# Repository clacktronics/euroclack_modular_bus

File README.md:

# Euroclack Modular Power

The set of boards in this repository are designed for building the power bus for a Eurorack synthesizer. They have been produced within the constraints of 100x100mm which is the size cheap PCB pool manufacturers usually use for their cheapest service.

| Folder   | Type   | Description   | Status  |
| -------- | ------ | ------------- | --------|
| 5V_supply   | DC/DC supply | Will produce a 5v rail on the power bus from 12V | Untested prototype |
| 6_way_bus | Utility | 6 way extension of eurorack IDC | Untested prototype |
| barrel_jack_panel | Panel | Barrel input for DC voltage or AC wall wart | Not Started |
| delay_start | Utility | Takes in power and outputs power at a delay | Not Started |
| linear_pu | AC/DC supply | Traditional Linear PSU | Untested prototype |
| meanwell_rddw20f-12_psu | DC/DC supply | Takes a single supply and output +-12V | Layout |
| switch_status_panel | Utility | simple panel that shows LED for power rails and switch for turning on and off | Not started|
| wall_wart_linear_psu | AC/DC supply | when no centre tap available, for example an AC wall wart or non-CT transformer. | Not started |

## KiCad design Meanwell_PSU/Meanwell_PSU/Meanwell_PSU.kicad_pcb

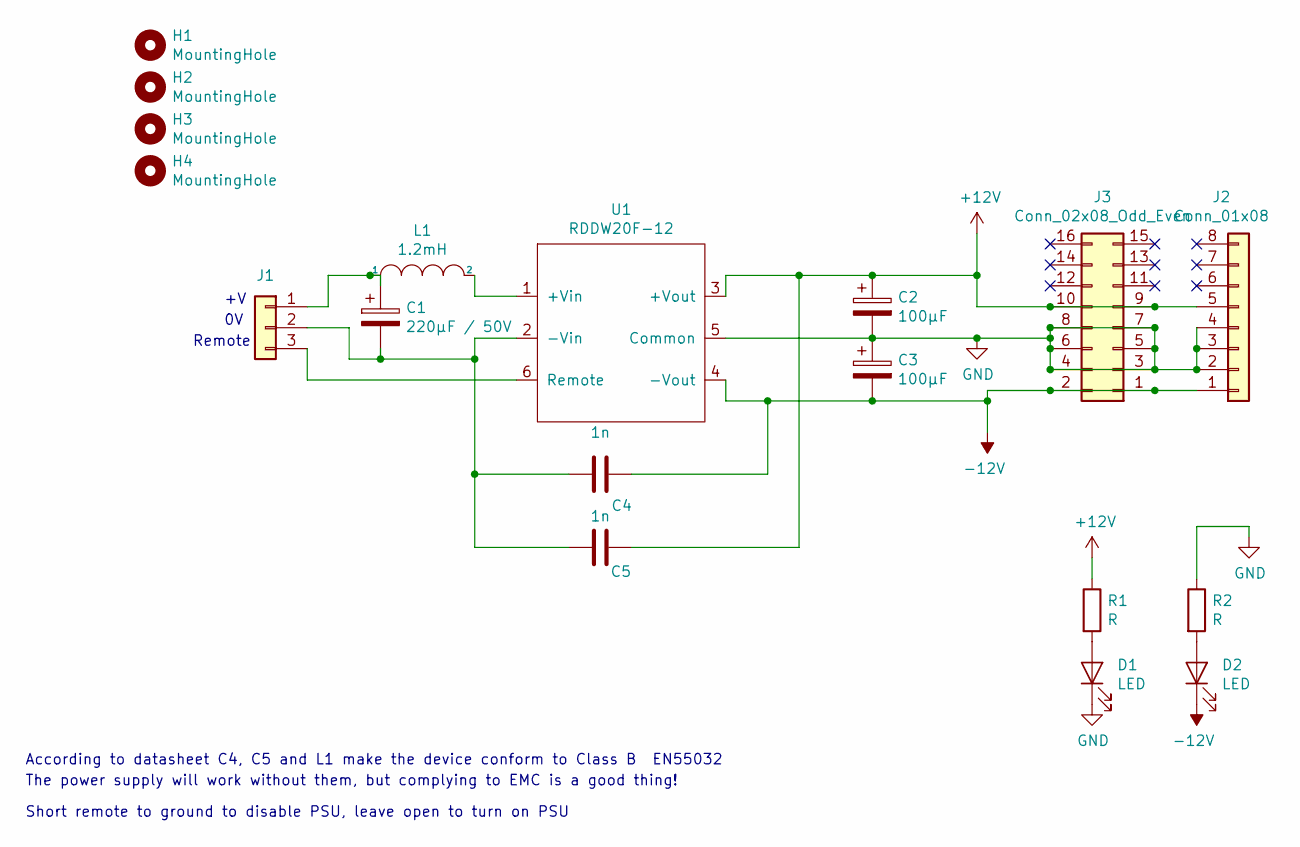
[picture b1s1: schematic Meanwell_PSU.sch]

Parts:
C1: 220μF / 50V; C_TH_Elec_5mm_P2mm
C2, C3: 100μF; C_TH_Elec_5mm_P2mm
C4, C5: 1n; C_TH_Disc_P5.00mm
D1, D2: LED; LED_D3.0mm
H1, H2, H3, H4: MountingHole; MountingHole_3.2mm_M3
J1: Conn_01x03; PhoenixContact_MSTBA_2,5_3-G-5,08_1x03_P5.08mm_Horizontal
J2: Conn_01x08; PinSocket_1x08_P2.54mm_Vertical
J3: Conn_02x08_Odd_Even; Eurorack-IDC-Header
L1: 1.2mH; L_Radial_D7.0mm_P3.00mm
R1, R2: R; R_TH_Axial_250mw_P10.16mm_Horizontal
U1: RDDW20F-12; RDDW20F

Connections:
+12V: C2.1, C5.1, J2.5, J3.9, J3.10, R1.1, U1.3 (+Vout)
-12V: C3.2, C4.1, D2.1 (K), J2.1, J3.1, J3.2, U1.4 (-Vout)
GND: C2.2, C3.1, D1.1 (K), J2.2, J2.3, J2.4, J3.3, J3.4, J3.5, J3.6, J3.7, J3.8, R2.1, U1.5 (Common)
unnamed: C1.1, J1.1, L1.1
unnamed: C1.2, C4.2, C5.2, J1.2, U1.2 (-Vin)
unnamed: D1.2 (A), R1.2
unnamed: D2.2 (A), R2.2
unnamed: J1.3, U1.6 (Remote)
unnamed: L1.2, U1.1 (+Vin)

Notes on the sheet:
Remote
According to datasheet C4, C5 and L1 make the device conform to Class B EN55032
The power supply will work without them, but complying to EMC is a good thing!
Short remote to ground to disable PSU, leave open to turn on PSU

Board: 2 copper layers, 18 parts (0 on the bottom side), 9 nets, no tracks yet.

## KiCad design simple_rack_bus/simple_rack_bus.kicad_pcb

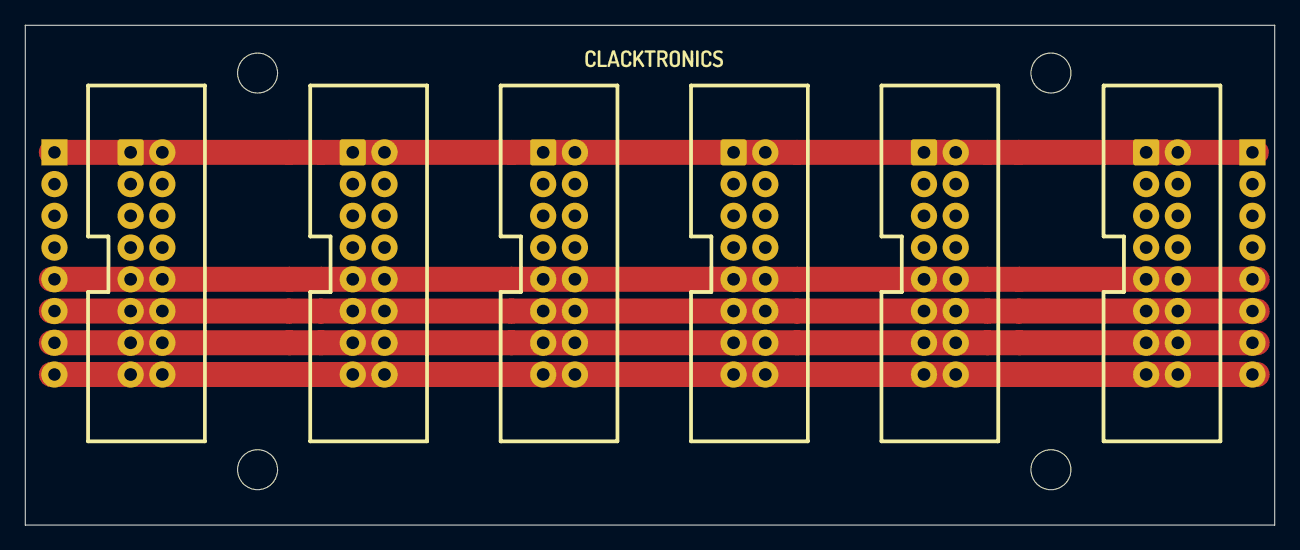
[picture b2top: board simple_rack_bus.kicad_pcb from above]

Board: 2 copper layers, 100.0 x 40.0 mm, 12 parts (0 on the bottom side), 6 nets.

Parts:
H1, H2, H3, H4: MountingHole; MountingHole_3.2mm_M3
J1, J2, J3, J4, J5, J6: Conn_02x08_Odd_Even; Eurorack-IDC-Header
J7, J8: Conn_01x08; PinHeader_1x08_P2.54mm_Vertical

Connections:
-12V: J1.1, J1.2, J2.1, J2.2, J3.1, J3.2, J4.1, J4.2, J5.1, J5.2, J6.1, J6.2, J7.1, J8.1
GND: J1.3, J1.4, J1.5, J1.6, J1.7, J1.8, J2.3, J2.4, J2.5, J2.6, J2.7, J2.8, J3.3, J3.4, J3.5, J3.6, J3.7, J3.8, J4.3, J4.4, J4.5, J4.6, J4.7, J4.8, J5.3, J5.4, J5.5, J5.6, J5.7, J5.8, J6.3, J6.4, J6.5, J6.6, J6.7, J6.8, J7.2, J7.3, J7.4, J8.2, J8.3, J8.4
unnamed: J1.9, J1.10, J2.9, J2.10, J3.9, J3.10, J4.9, J4.10, J5.9, J5.10, J6.9, J6.10, J7.5, J8.5
unnamed: J1.11, J1.12, J2.11, J2.12, J3.11, J3.12, J4.11, J4.12, J5.11, J5.12, J6.11, J6.12, J7.6, J8.6
unnamed: J1.13, J1.14, J2.13, J2.14, J3.13, J3.14, J4.13, J4.14, J5.13, J5.14, J6.13, J6.14, J7.7, J8.7
unnamed: J1.15, J1.16, J2.15, J2.16, J3.15, J3.16, J4.15, J4.16, J5.15, J5.16, J6.15, J6.16, J7.8, J8.8

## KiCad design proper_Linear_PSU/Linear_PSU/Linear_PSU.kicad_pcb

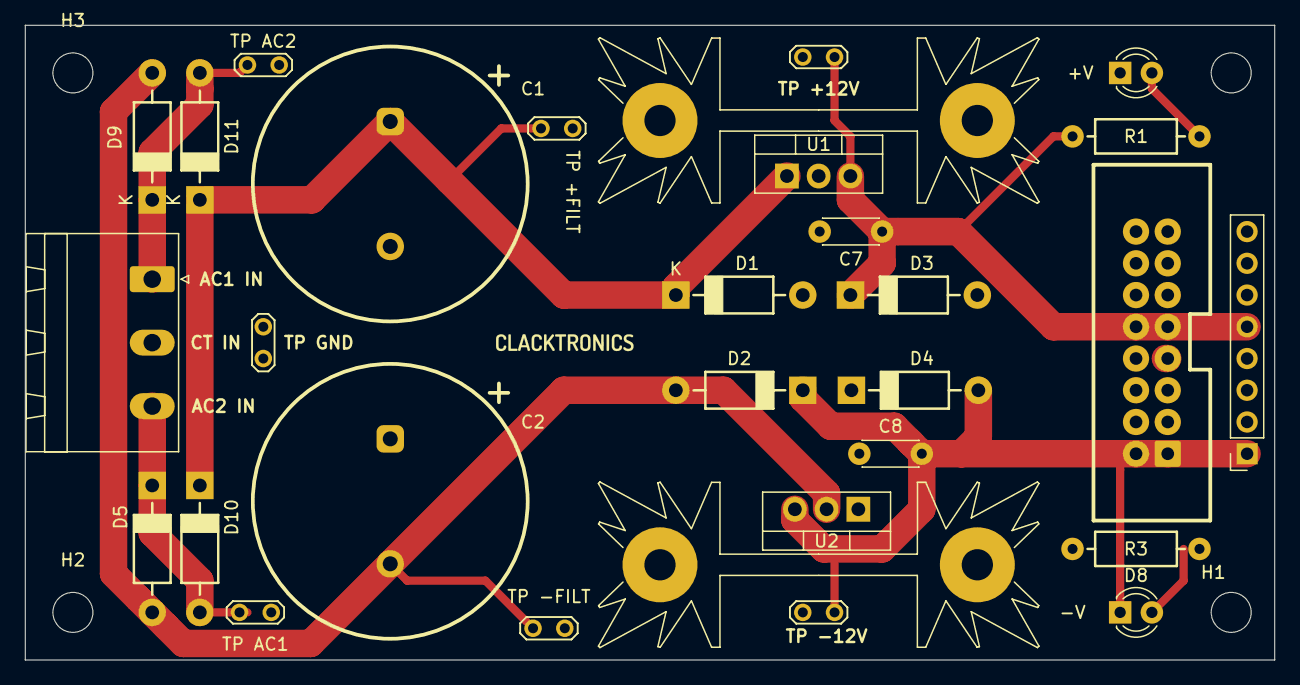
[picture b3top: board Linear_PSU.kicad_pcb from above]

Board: 2 copper layers, 100.0 x 50.8 mm, 34 parts (0 on the bottom side), 9 nets.

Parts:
C1, C2: 4.7-10mF 50V; C_TH_Elec_22mm_10mm
C7, C8: 100n; C_TH_Disc_P5.00mm
D1, D2, D3, D4, D5, D9, D10, D11: 1N4001; D_TH_DO-41_P10.16mm
D6, D8: LED; LED_D3.0mm
H1, H2, H3, H4: MountingHole; MountingHole_3.2mm_M3
HS1, HS2: Heatsink; Heatsink_Fischer_SK104-STC-STIC_35x13mm_2xDrill2.5mm
J1: Conn_01x03; PhoenixContact_MSTBA_2,5_3-G-5,08_1x03_P5.08mm_Horizontal
J2: Conn_02x08_Odd_Even; Eurorack-IDC-Header
J3: Conn_01x08; PinSocket_1x08_P2.54mm_Vertical
R1, R3: 4k7; R_TH_Axial_250mw_P10.16mm_Horizontal
TP+12V1: TP_+12v; TestPoint_2Pads_Pitch2.54mm_Drill0.8mm
TP-12V1: TP_-12v; TestPoint_2Pads_Pitch2.54mm_Drill0.8mm
TP_AC1: TP_AC1; TestPoint_2Pads_Pitch2.54mm_Drill0.8mm
TP_AC2: TP_AC2; TestPoint_2Pads_Pitch2.54mm_Drill0.8mm
TP_FILT+1: TP_FILT+; TestPoint_2Pads_Pitch2.54mm_Drill0.8mm
TP_FILT-1: TP_FILT-; TestPoint_2Pads_Pitch2.54mm_Drill0.8mm
TP_GND1: TP_GND; TestPoint_2Pads_Pitch2.54mm_Drill0.8mm
U1: L7812; TO-220-3_Vertical
U2: L7912; TO-220-3_Vertical

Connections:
+12V: C7.1, D1.2, D3.1, J2.9, J2.10, J3.5, R1.1, TP+12V1.1, U1.3
-12V: C8.2, D2.1, D4.2, D8.1, J2.1, J2.2, J3.1, TP-12V1.1, U2.3
/AC1: D5.1, D10.2, J1.3, TP_AC1.1
/AC2: D9.1, D11.2, J1.1, TP_AC2.1
GND: C1.2, C2.1, C7.2, C8.1, D3.2, D4.1, D6.1, J1.2, J2.3, J2.4, J2.5, J2.6, J2.7, J2.8, J3.3, R3.1, TP_GND1.1, U1.2, U2.1
unnamed: C1.1, D1.1, D10.1, D11.1, TP_FILT+1.1, U1.1
unnamed: C2.2, D2.2, D5.2, D9.2, TP_FILT-1.1, U2.2
unnamed: D6.2, R1.2
unnamed: D8.2, R3.2

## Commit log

2019-10-30 Initial idea
2019-10-30 Project organised
